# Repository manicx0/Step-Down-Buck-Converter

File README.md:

# LM5116 Wide-Range Synchronous Buck Converter

A variable-output synchronous buck converter designed around the Texas Instruments
LM5116 controller, capable of delivering 3 V to ~41 V output at up to 8 A from
a 45 V input rail. Designed as an open-source hardware project for industrial,
bench-supply, and automotive applications.

> ⚠️ **Status: Work In Progress — not yet validated on hardware.**
> Schematic is complete and under review. PCB layout not yet started.

---

## Specifications

| Parameter | Value |
|---|---|
| Input Voltage | Up to 45 V |
| Output Voltage | 3 V – ~41 V (continuously variable) |
| Maximum Output Current | 8 A |
| Switching Frequency | ~200 kHz |
| Control Method | Emulated peak current mode |
| Topology | Synchronous Buck |
| Controller IC | Texas Instruments LM5116MH/NOPB |

---

## Key Design Decisions

### Variable Output
Output voltage is set by a feedback divider on the FB pin (pin 9).
RFB1 (R4 = 1.21 kΩ) is fixed. RFB2 is implemented as a 50 kΩ potentiometer (R3)
in series with a 1.78 kΩ fixed resistor (R30), which hard-limits the minimum
output to 3 V even when the pot is at 0 Ω.
VOUT = 1.215 V × (1 + RFB2 / RFB1)

At RFB2 = 1.78 kΩ → VOUT = 3.01 V (minimum)
At RFB2 = 51.78 kΩ → VOUT ≈ 53 V (capped by VIN in practice)

### Slope Compensation (RRAMP)
For output voltages above 7.5 V, the LM5116 datasheet (Section 7.2.2.16)
requires a resistor from the RAMP pin to VCC to add slope compensation and
prevent subharmonic oscillation. R15 = 120 kΩ is connected between
pin 5 (RAMP) and pin 16 (VCC), sized for a nominal output of ~24 V.

### Emulated Current Ramp Capacitor

CRAMP = (gm × L) / (A × RS)
= (5 µA/V × 18 µH) / (10 V/V × 10 mΩ)
= 900 pF → 1 nF COG selected (C3)

### MOSFET Selection
Both high-side (Q3) and low-side (Q4) use the Infineon BSC070N10NS5,
a 100 V / 70 mΩ N-channel MOSFET in a TO-252 package. The 100 V rating
provides adequate margin over the 45 V input accounting for switching
transients and ringing.

Key references from the LM5116 datasheet (SNVS499I):
- Section 6.3.6 — Ramp generator and RRAMP justification
- Section 7.2.2.11 — Output voltage divider equations
- Section 7.2.2.16 — Comprehensive equations for VOUT > 7.5 V
- Section 7.4 — Layout guidelines

---

## ⚠️ Warnings & Limitations

- Maximum output voltage is bounded by the 450 ns forced HO off-time:
  `VOUT_max = VIN × (1 − 450 ns × fSW)`. At 45 V input and 200 kHz,
  this is approximately 41 V — not a true 45 V output.
- VCCX (pin 17) must be connected to GND if the external bias feature
  is not used. Leaving it floating causes unpredictable VCC behavior.
- This design has not yet been validated on hardware.
  Use at your own risk in any safety-critical application.
- High voltage and high current. Always verify polarity of electrolytic
  output capacitors before powering on.

---

## Acknowledgements

- Texas Instruments LM5116 datasheet (SNVS499I) — design procedure
  and equations throughout Section 7
- TI WEBENCH Power Designer for cross-checking component values
- Infineon BSC070N10NS5 datasheet for MOSFET loss calculations

---

## License

This project is released under the **CERN Open Hardware Licence Version 2 –
Weakly Reciprocal (CERN-OHL-W-2.0)**.

You are free to study, modify, and distribute this hardware design.
If you distribute modified versions, you must use the same licence.

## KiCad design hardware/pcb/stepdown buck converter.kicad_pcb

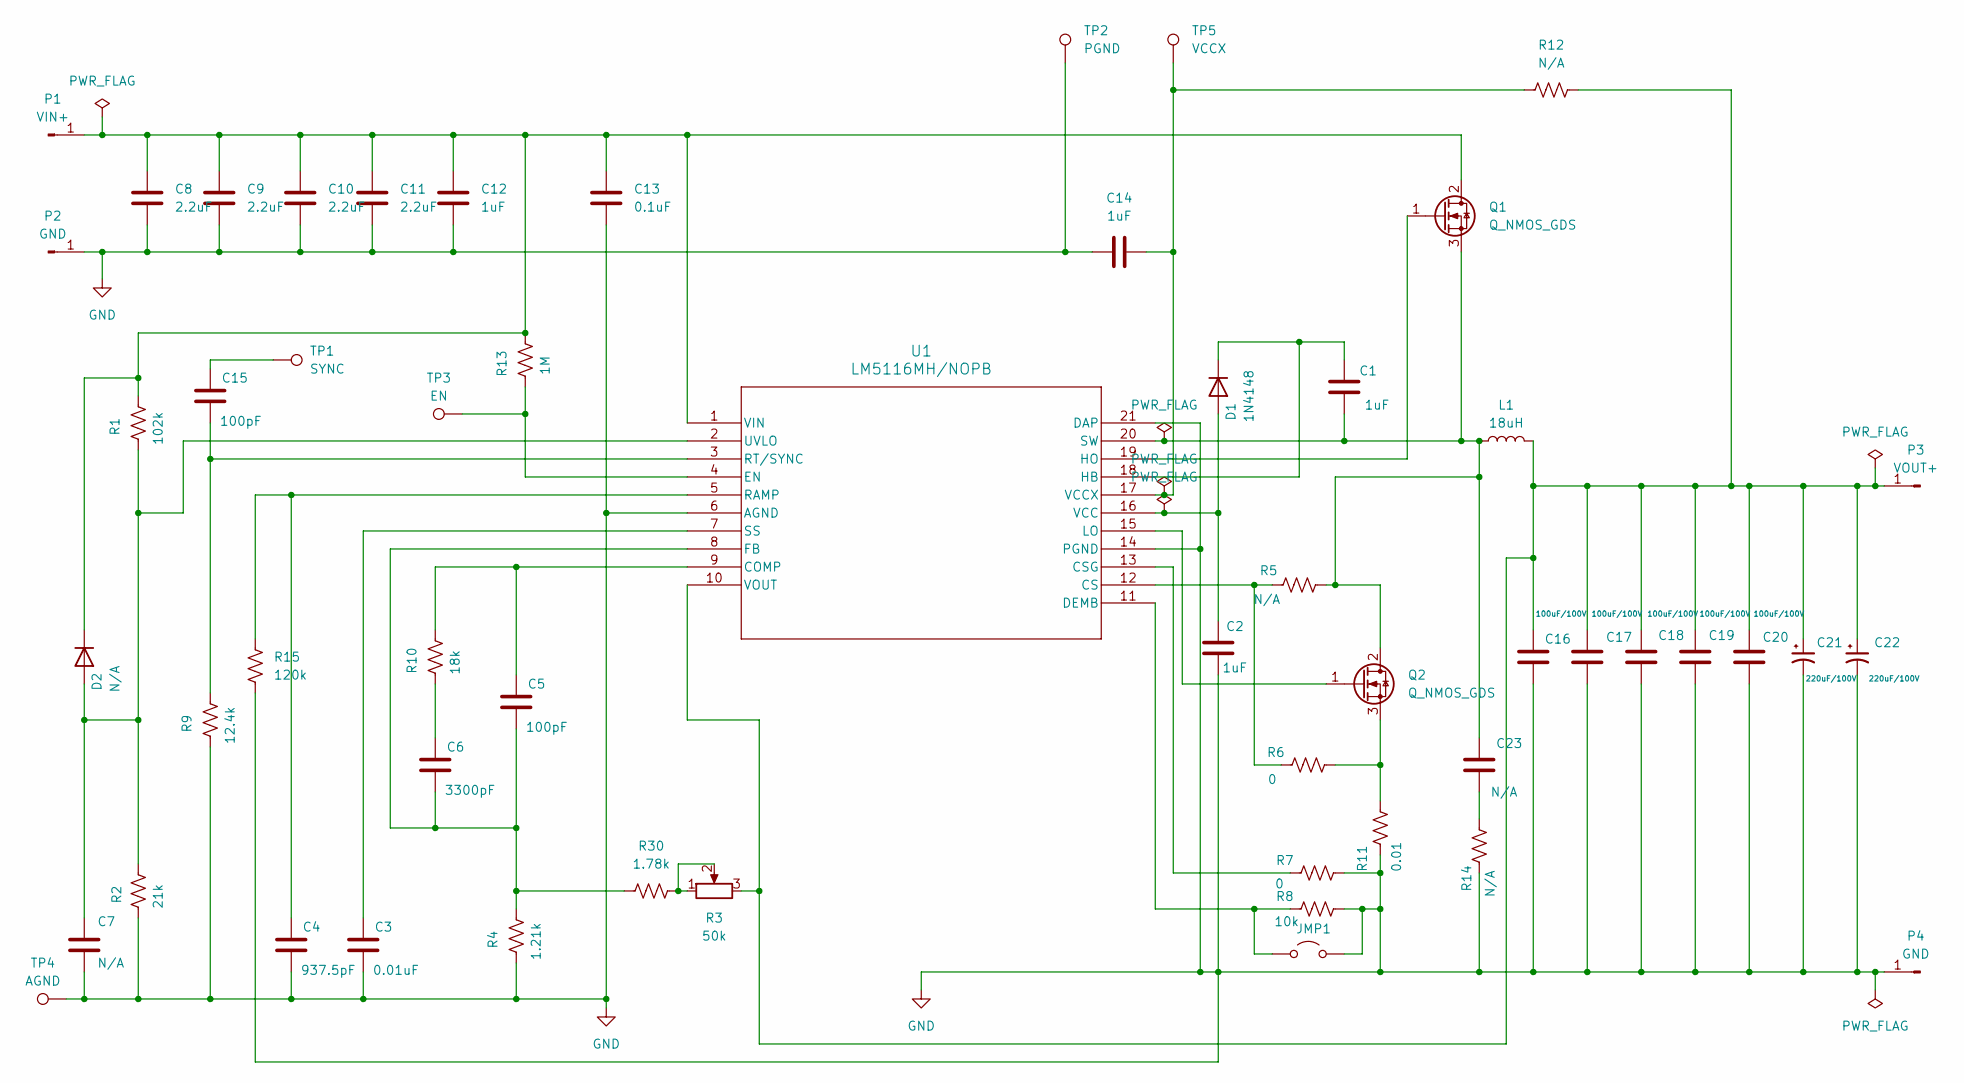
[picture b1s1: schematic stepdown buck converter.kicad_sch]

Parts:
C1, C2, C12, C14: 1uF; C_0805_2012Metric
C3: 0.01uF; C_0805_2012Metric
C4: 937.5pF; C_0805_2012Metric
C5, C15: 100pF; C_0805_2012Metric
C6: 3300pF; C_0805_2012Metric
C7, C23: N/A; C_0805_2012Metric
C8, C9, C10, C11: 2.2uF; C_0805_2012Metric
C13: 0.1uF; C_0805_2012Metric
C16, C17, C18, C19, C20: 100uF/100V; C_0805_2012Metric
C21, C22: 220uF/100V; CP_Elec_8x5.4
D1: 1N4148; D_SOD-123
D2: N/A; D_SOD-123
JMP1: SolderJumper-2_P1.3mm_Bridged2Bar_Pad1.0x1.5mm
L1: 18uH; L_12x12mm_H6mm
P1: VIN+; SolderWire-1.5sqmm_1x01_D1.7mm_OD3mm
P2, P4: GND; SolderWire-1.5sqmm_1x01_D1.7mm_OD3mm
P3: VOUT+; SolderWire-1.5sqmm_1x01_D1.7mm_OD3mm
Q1, Q2: Q_NMOS_GDS; TO-220-3_Vertical
R1: 102k; R_0805_2012Metric_Pad1.20x1.40mm_HandSolder
R2: 21k; R_0805_2012Metric_Pad1.20x1.40mm_HandSolder
R3: 50k; Potentiometer_Bourns_3214W_Vertical
R4: 1.21k; R_0805_2012Metric_Pad1.20x1.40mm_HandSolder
R5, R12, R14: N/A; R_0805_2012Metric_Pad1.20x1.40mm_HandSolder
R6, R7: 0; R_0805_2012Metric_Pad1.20x1.40mm_HandSolder
R8: 10k; R_0805_2012Metric_Pad1.20x1.40mm_HandSolder
R9: 12.4k; R_0805_2012Metric_Pad1.20x1.40mm_HandSolder
R10: 18k; R_0805_2012Metric_Pad1.20x1.40mm_HandSolder
R11: 0.01; R_0805_2012Metric_Pad1.20x1.40mm_HandSolder
R13: 1M; R_0805_2012Metric_Pad1.20x1.40mm_HandSolder
R15: 120k; R_0805_2012Metric_Pad1.20x1.40mm_HandSolder
R30: 1.78k; R_0805_2012Metric_Pad1.20x1.40mm_HandSolder
TP1: SYNC; TestPoint_Pad_D2.0mm
TP2: PGND; TestPoint_Pad_D2.0mm
TP3: EN; TestPoint_Pad_D2.0mm
TP4: AGND; TestPoint_Pad_D2.0mm
TP5: VCCX; TestPoint_Pad_D2.0mm
U1: LM5116MH/NOPB; MXA20A_TEX

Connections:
GND: C2.2, C3.2, C4.2, C7.2, C8.1, C9.1, C10.1, C11.1, C12.1, C13.1, C14.1, C16.2, C17.2, C18.2, C19.2, C20.2, C21.2, C22.2, JMP1.2 (B), P2.1 (Pin_1_1), P4.1 (Pin_1_1), R2.2, R4.2, R7.1, R8.1, R9.2, R11.2, R14.2, R15.2, TP2.1 (1_1), TP4.1 (1_1), U1.6 (AGND), U1.14 (PGND), U1.21 (DAP)
unnamed: C6.1, R10.2
unnamed: C15.1, TP1.1 (1_1)
unnamed: C23.2, R14.1
unnamed: C2.1, D1.2 (A), U1.16 (VCC)
unnamed: C1.1, D1.1 (K), U1.18 (HB)
unnamed: C7.1, D2.2 (A), R1.2, R2.1, U1.2 (UVLO)
unnamed: C8.2, C9.2, C10.2, C11.2, C12.2, C13.2, D2.1 (K), P1.1 (Pin_1_1), Q1.2 (D), R1.1, R13.1, U1.1 (VIN)
unnamed: JMP1.1 (A), R8.2, U1.11 (DEMB)
unnamed: C16.1, C17.1, C18.1, C19.1, C20.1, C21.1, C22.1, L1.2, P3.1 (Pin_1_1), R3.3, R12.1, U1.10 (VOUT)
unnamed: Q1.1 (G), U1.19 (HO)
unnamed: C1.2, C23.1, L1.1, Q1.3 (S), Q2.2 (D), R5.1, U1.20 (SW)
unnamed: Q2.1 (G), U1.15 (LO)
unnamed: Q2.3 (S), R6.1, R11.1
unnamed: R3.1, R3.2, R30.2
unnamed: C5.1, R10.1, U1.9 (COMP)
unnamed: R5.2, R6.2, U1.12 (CS)
unnamed: R7.2, U1.13 (CSG)
unnamed: R13.2, TP3.1 (1_1), U1.4 (EN)
unnamed: C5.2, C6.2, R4.1, R30.1, U1.8 (FB)
unnamed: C4.1, R15.1, U1.5 (RAMP)
unnamed: C15.2, R9.1, U1.3 (RT/SYNC)
unnamed: C3.1, U1.7 (SS)
unnamed: C14.2, R12.2, TP5.1 (1_1), U1.17 (VCCX)

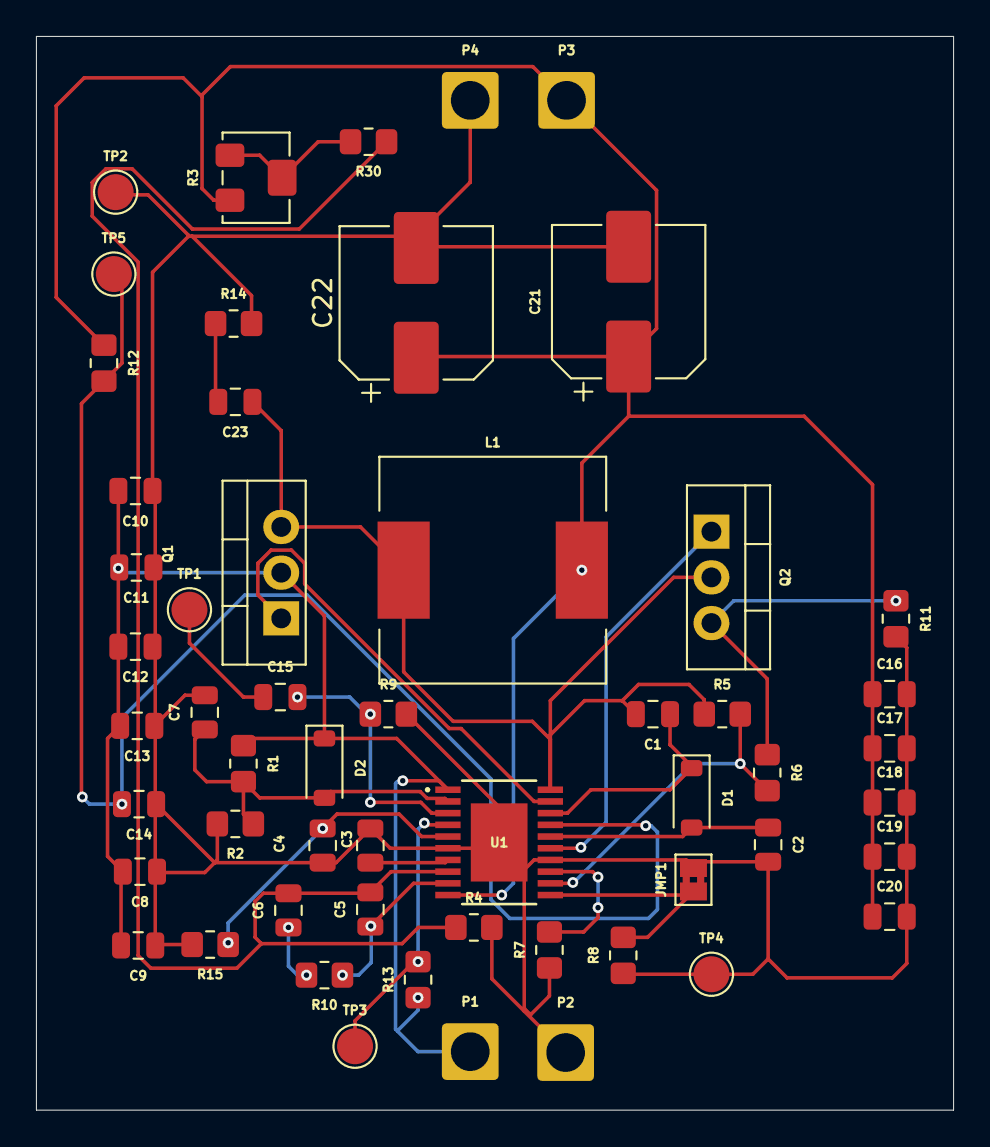
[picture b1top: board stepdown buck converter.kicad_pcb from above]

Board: 2 copper layers, 51.0 x 59.7 mm, 55 parts (0 on the bottom side), 24 nets.
